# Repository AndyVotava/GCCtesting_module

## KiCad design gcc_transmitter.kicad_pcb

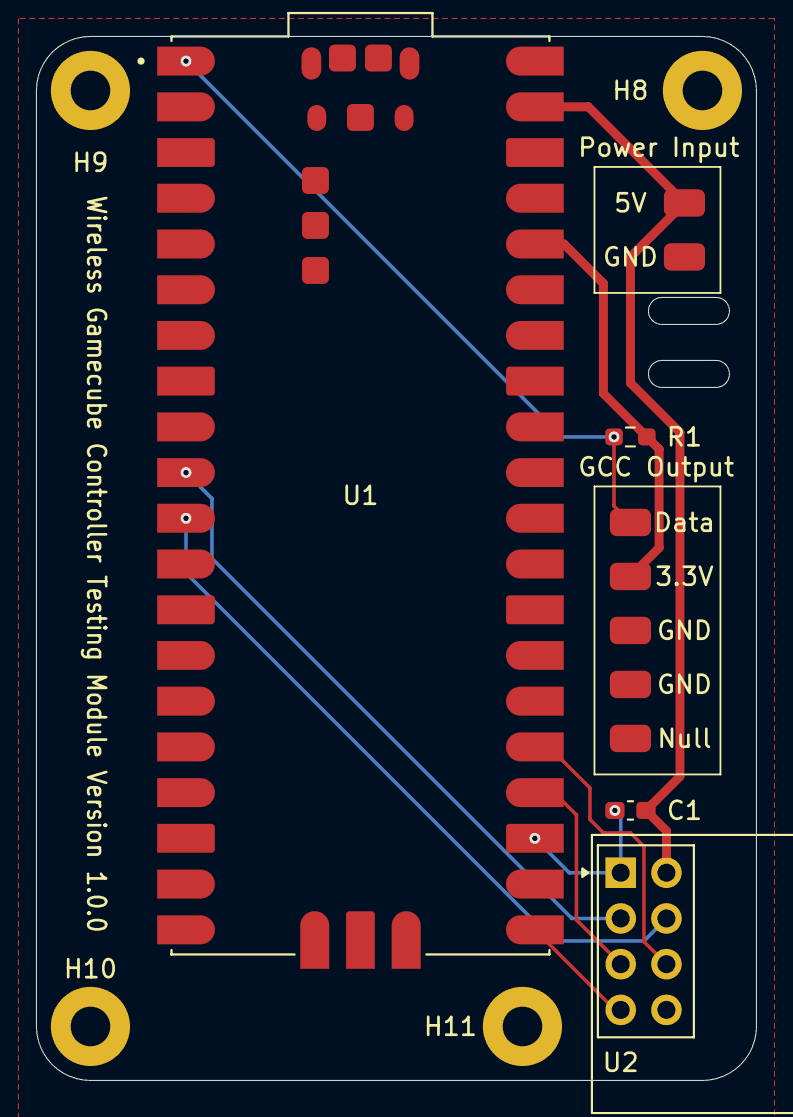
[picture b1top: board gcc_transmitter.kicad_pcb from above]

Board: 2 copper layers, 40.0 x 58.0 mm, 15 parts (0 on the bottom side), 9 nets.

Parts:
3.3V, 5V: MountingHole_Pad; PAD
C1: 10u; C_0603_1608Metric_Pad1.08x0.95mm_HandSolder
Data: MountingHole_Pad; PAD
GND: MountingHole_Pad; PAD
GND#2, GND#3: MountingHole_Pad; PAD
H8, H9, H10, H11: MountingHole_Pad; MountingHole_2.2mm_M2_Pad
Null: MountingHole_Pad; PAD
R1: 1k; R_0603_1608Metric_Pad0.98x0.95mm_HandSolder
U1: SC0915; Raspberry Pi Pico
U2: NRF24L01_Breakout; nRF24L01_Breakout

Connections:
+3V3: 3.3V.1, R1.1, U1.36 (3V3_OUT)
+5V: 5V.1, C1.1, U1.39 (VSYS), U2.2 (VCC)
/CE: U1.10 (GP7), U2.3 (CE)
/CS: U1.11 (GP8), U2.4 (~CSN)
/Data: Data.1, R1.2, U1.1 (GP0)
/RX/MISO: U1.21 (GP16), U2.7 (MISO)
/SCK: U1.24 (GP18), U2.5 (SCK)
/TX/MOSI: U1.25 (GP19), U2.6 (MOSI)
GND: C1.2, GND.1, GND#2.1, GND#3.1, H8.1, H9.1, H10.1, H11.1, U1.3 (GND), U1.8 (GND__1), U1.13 (GND__2), U1.18 (GND__3), U1.23 (GND__4), U1.28 (GND__5), U1.33 (AGND), U1.38 (GND__6), U1.A (USB_SHIELD), U1.B (USB_SHIELD__1), U1.C (USB_SHIELD__2), U1.D (USB_SHIELD__3), U1.D2 (GND__7), U2.1 (GND)

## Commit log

2024-08-13 deleted temp files
